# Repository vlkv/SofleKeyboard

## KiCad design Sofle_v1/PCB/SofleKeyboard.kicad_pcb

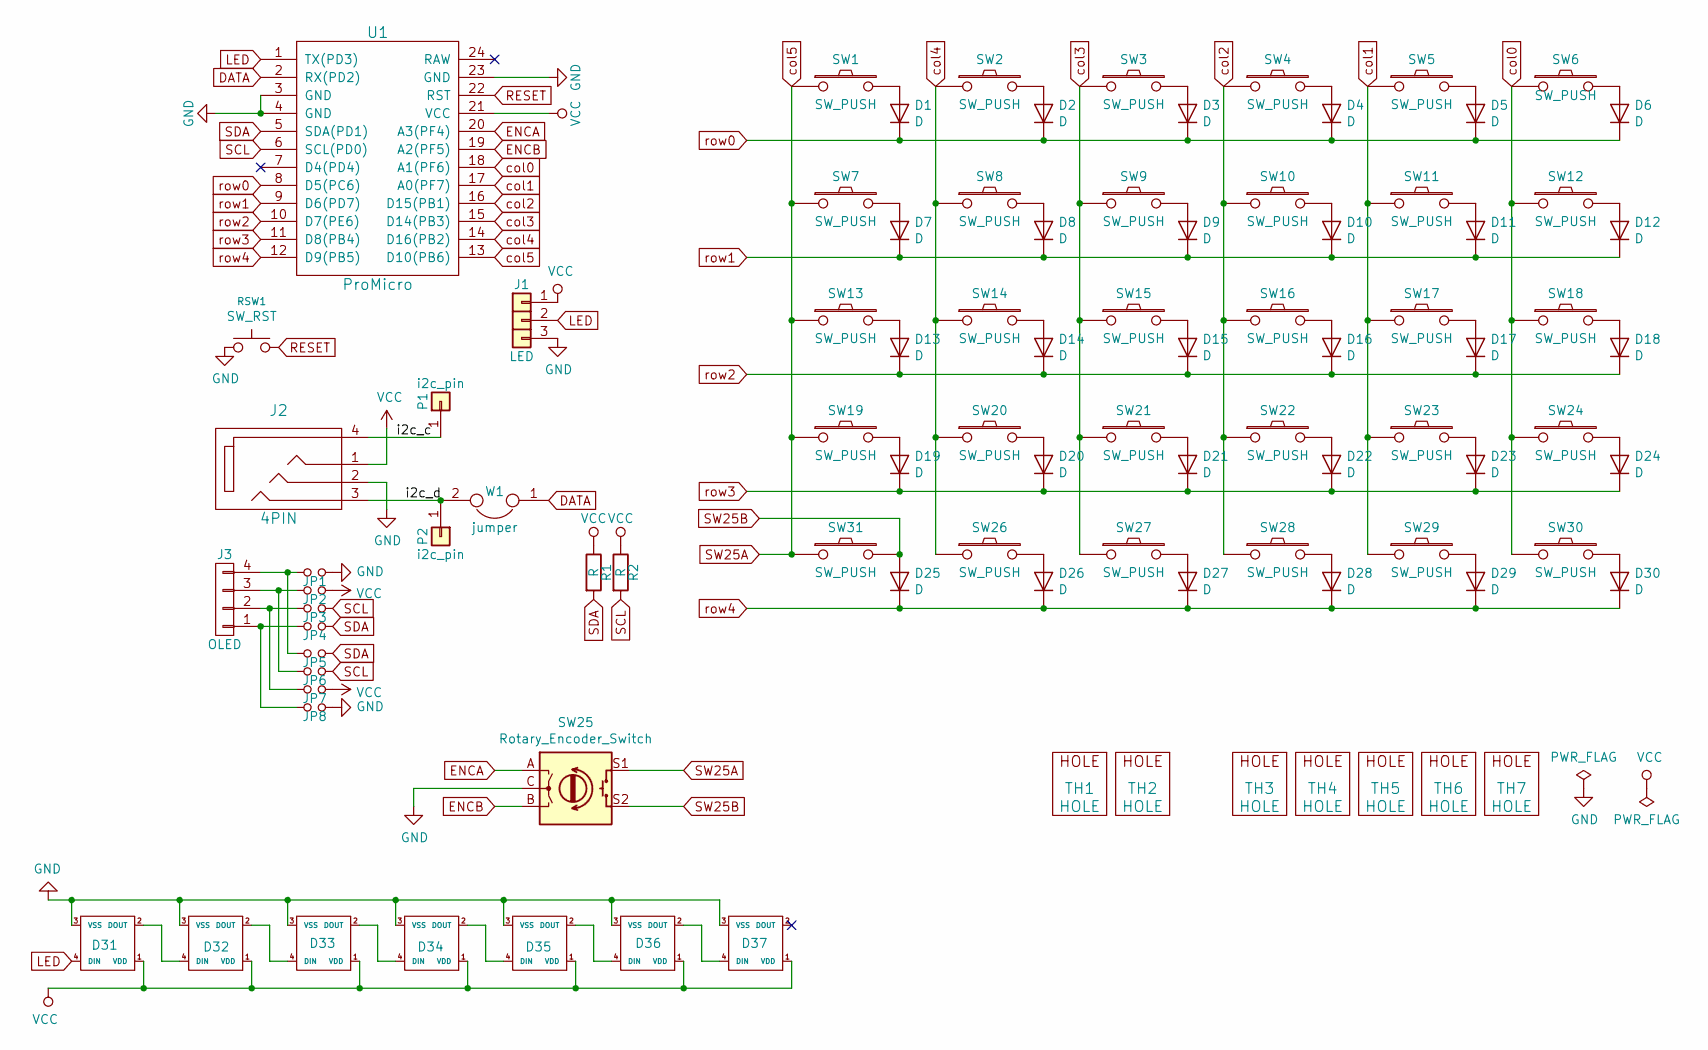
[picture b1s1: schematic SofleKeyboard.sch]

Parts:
D1, D2, D3, D4, D5, D6, D7, D8, D9, D10, D11, D12, D13, D14, D15, D16, D17, D18, D19, D20, D21, D22, D23, D24, D25, D26, D27, D28, D29, D30: D; Diode_SOD123
D31, D32, D33, D34, D35, D36, D37: SK6812MINI; YS-SK6812MINI-E_backlight
J1: LED
J2: 4PIN; MJ-4PP-9
J3: OLED; OLED_4Pin
JP1, JP2, JP3, JP4, JP5, JP6, JP7, JP8: Jumper_NO_Small; Jumper
P1, P2: i2c_pin; 1pin_conn
R1, R2: R; RESISTOR_mini
RSW1: SW_RST; TACT_SWITCH_TVBP06
SW1, SW2, SW3, SW4, SW5, SW6, SW7, SW8, SW9, SW10, SW11, SW12, SW13, SW14, SW15, SW16, SW17, SW18, SW19, SW20, SW21, SW22, SW23, SW24, SW26, SW27, SW28, SW29, SW30, SW31: SW_PUSH; CherryMX_Hotswap
SW25: Rotary_Encoder_Switch; RotaryEncoder_Alps_EC11E-Switch_Vertical_H20mm-keebio_modif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
TH1, TH2: HOLE; M2_HOLE_PCB
TH3, TH4, TH5, TH6, TH7: HOLE; HOLE_M2_TH
U1: ProMicro
W1: jumper; jumper_data

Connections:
/i2c_c: J2.4, P1.1
/i2c_d: J2.3, P2.1, W1.2
DATA: U1.2 (RX(PD2)), W1.1
ENCA: SW25.A, U1.20 (A3(PF4))
ENCB: SW25.B, U1.19 (A2(PF5))
GND: D31.3 (VSS), D32.3 (VSS), D33.3 (VSS), D34.3 (VSS), D35.3 (VSS), D36.3 (VSS), D37.3 (VSS), J1.3, J2.2, JP1.2, JP8.2, RSW1.1, SW25.C, U1.3 (GND), U1.4 (GND), U1.23 (GND)
LED: D31.4 (DIN), J1.2, U1.1 (TX(PD3))
unnamed: D1.2 (A), SW1.2
unnamed: D2.2 (A), SW2.2
unnamed: D3.2 (A), SW3.2
unnamed: D4.2 (A), SW4.2
unnamed: D5.2 (A), SW5.2
unnamed: D6.2 (A), SW6.2
unnamed: D7.2 (A), SW7.2
unnamed: D8.2 (A), SW8.2
unnamed: D9.2 (A), SW9.2
unnamed: D10.2 (A), SW10.2
unnamed: D11.2 (A), SW11.2
unnamed: D12.2 (A), SW12.2
unnamed: D13.2 (A), SW13.2
unnamed: D14.2 (A), SW14.2
unnamed: D15.2 (A), SW15.2
unnamed: D16.2 (A), SW16.2
unnamed: D17.2 (A), SW17.2
unnamed: D18.2 (A), SW18.2
unnamed: D19.2 (A), SW19.2
unnamed: D20.2 (A), SW20.2
unnamed: D21.2 (A), SW21.2
unnamed: D22.2 (A), SW22.2
unnamed: D23.2 (A), SW23.2
unnamed: D24.2 (A), SW24.2
unnamed: D26.2 (A), SW26.2
unnamed: D27.2 (A), SW27.2
unnamed: D28.2 (A), SW28.2
unnamed: D29.2 (A), SW29.2
unnamed: D30.2 (A), SW30.2
unnamed: D31.2 (DOUT), D32.4 (DIN)
unnamed: D32.2 (DOUT), D33.4 (DIN)
unnamed: D33.2 (DOUT), D34.4 (DIN)
unnamed: D34.2 (DOUT), D35.4 (DIN)
unnamed: D35.2 (DOUT), D36.4 (DIN)
unnamed: D36.2 (DOUT), D37.4 (DIN)
unnamed: J3.1, JP4.1, JP8.1
unnamed: J3.2, JP3.1, JP7.1
unnamed: J3.3, JP2.1, JP6.1
unnamed: J3.4, JP1.1, JP5.1
RESET: RSW1.2, U1.22 (RST)
SCL: JP3.2, JP6.2, R2.2, U1.6 (SCL(PD0))
SDA: JP4.2, JP5.2, R1.2, U1.5 (SDA(PD1))
SW25A: SW1.1, SW7.1, SW13.1, SW19.1, SW25.S1, SW31.1, U1.13 (D10(PB6))
SW25B: D25.2 (A), SW25.S2, SW31.2
VCC: D31.1 (VDD), D32.1 (VDD), D33.1 (VDD), D34.1 (VDD), D35.1 (VDD), D36.1 (VDD), D37.1 (VDD), J1.1, J2.1, JP2.2, JP7.2, R1.1, R2.1, U1.21 (VCC)
col0: SW6.1, SW12.1, SW18.1, SW24.1, SW30.1, U1.18 (A1(PF6))
col1: SW5.1, SW11.1, SW17.1, SW23.1, SW29.1, U1.17 (A0(PF7))
col2: SW4.1, SW10.1, SW16.1, SW22.1, SW28.1, U1.16 (D15(PB1))
col3: SW3.1, SW9.1, SW15.1, SW21.1, SW27.1, U1.15 (D14(PB3))
col4: SW2.1, SW8.1, SW14.1, SW20.1, SW26.1, U1.14 (D16(PB2))
row0: D1.1 (K), D2.1 (K), D3.1 (K), D4.1 (K), D5.1 (K), D6.1 (K), U1.8 (D5(PC6))
row1: D7.1 (K), D8.1 (K), D9.1 (K), D10.1 (K), D11.1 (K), D12.1 (K), U1.9 (D6(PD7))
row2: D13.1 (K), D14.1 (K), D15.1 (K), D16.1 (K), D17.1 (K), D18.1 (K), U1.10 (D7(PE6))
row3: D19.1 (K), D20.1 (K), D21.1 (K), D22.1 (K), D23.1 (K), D24.1 (K), U1.11 (D8(PB4))
row4: D25.1 (K), D26.1 (K), D27.1 (K), D28.1 (K), D29.1 (K), D30.1 (K), U1.12 (D9(PB5))

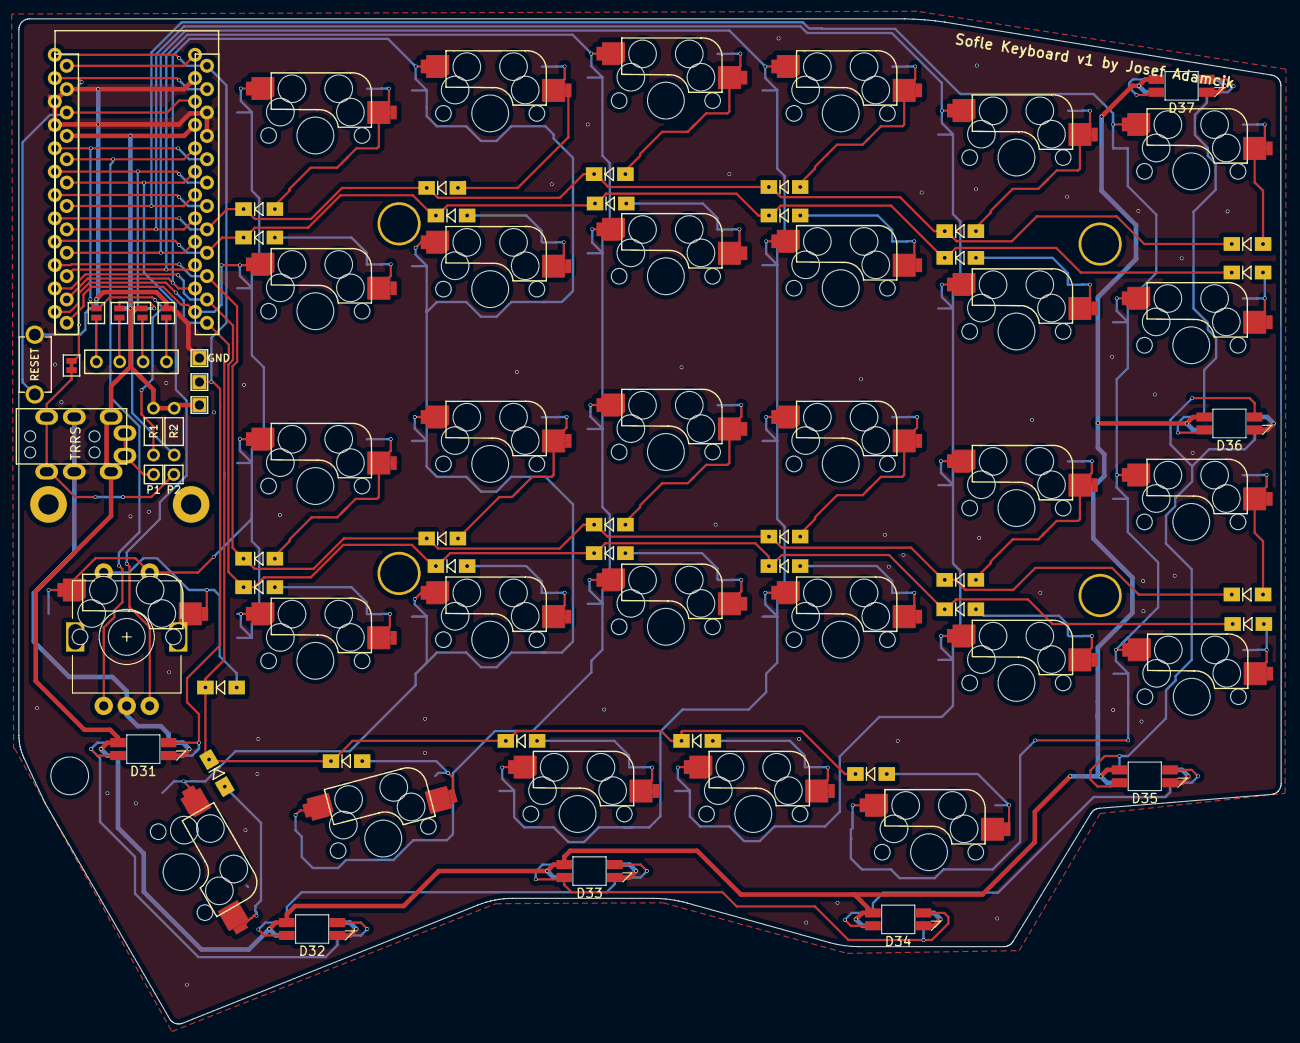
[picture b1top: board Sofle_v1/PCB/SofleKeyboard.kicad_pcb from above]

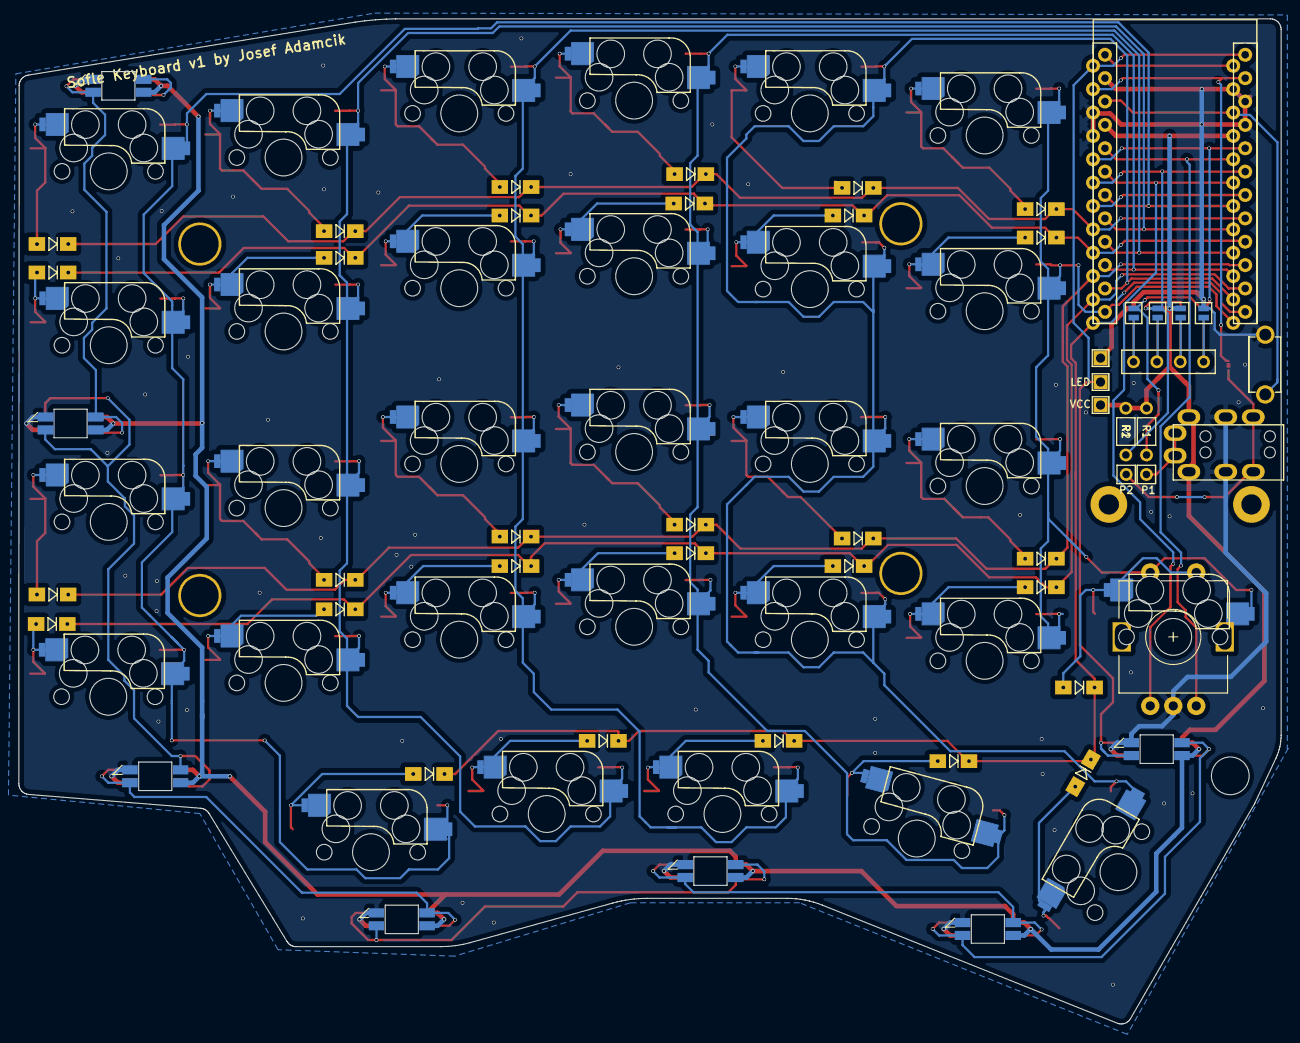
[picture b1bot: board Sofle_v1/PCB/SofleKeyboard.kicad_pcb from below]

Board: 2 copper layers, 137.2 x 109.2 mm, 93 parts (4 on the bottom side), 62 nets.

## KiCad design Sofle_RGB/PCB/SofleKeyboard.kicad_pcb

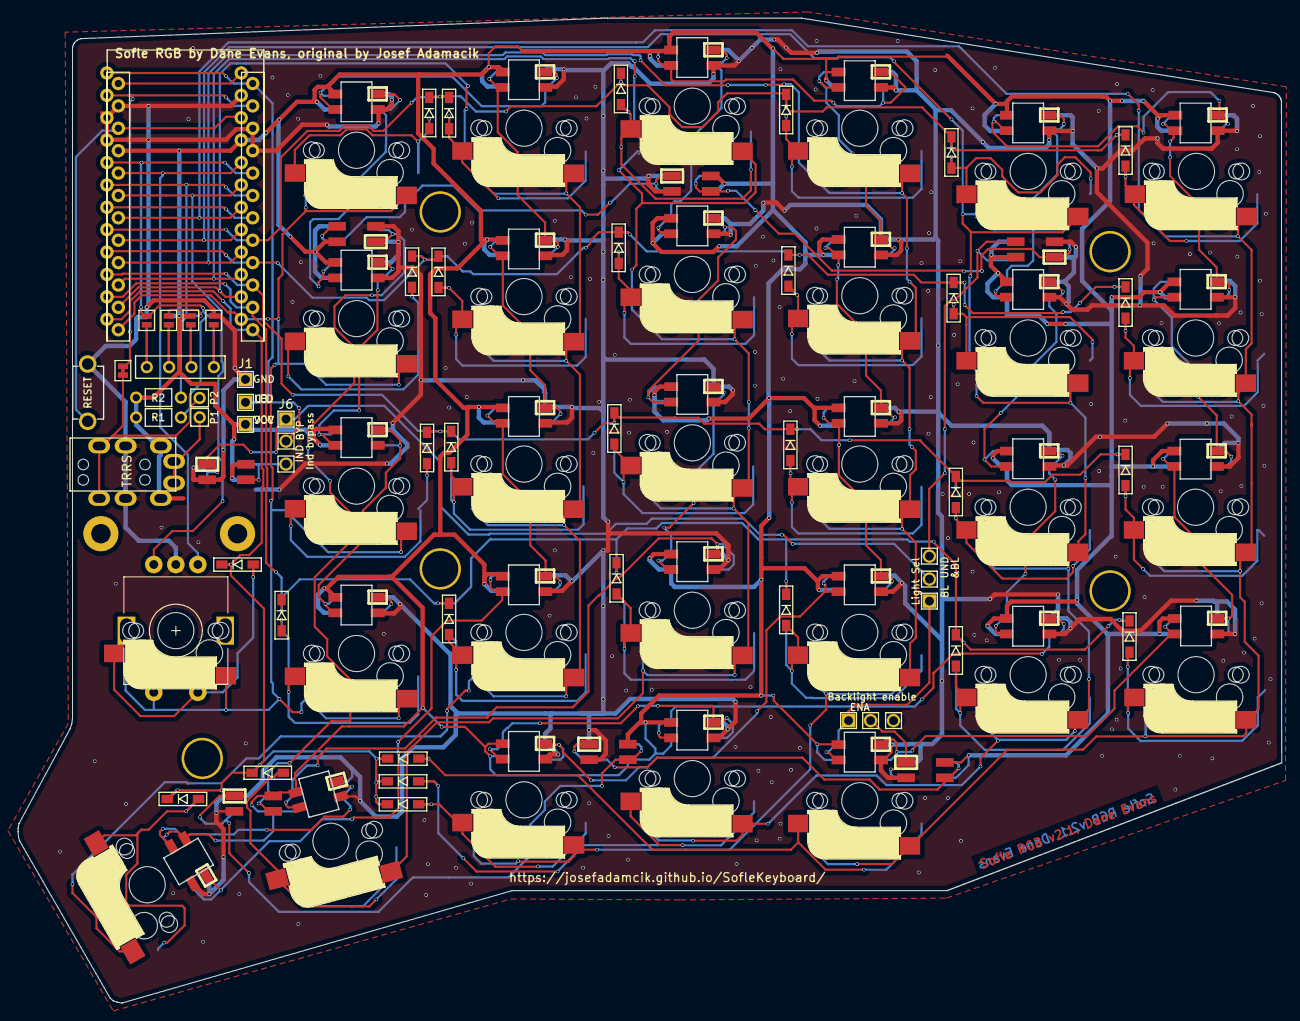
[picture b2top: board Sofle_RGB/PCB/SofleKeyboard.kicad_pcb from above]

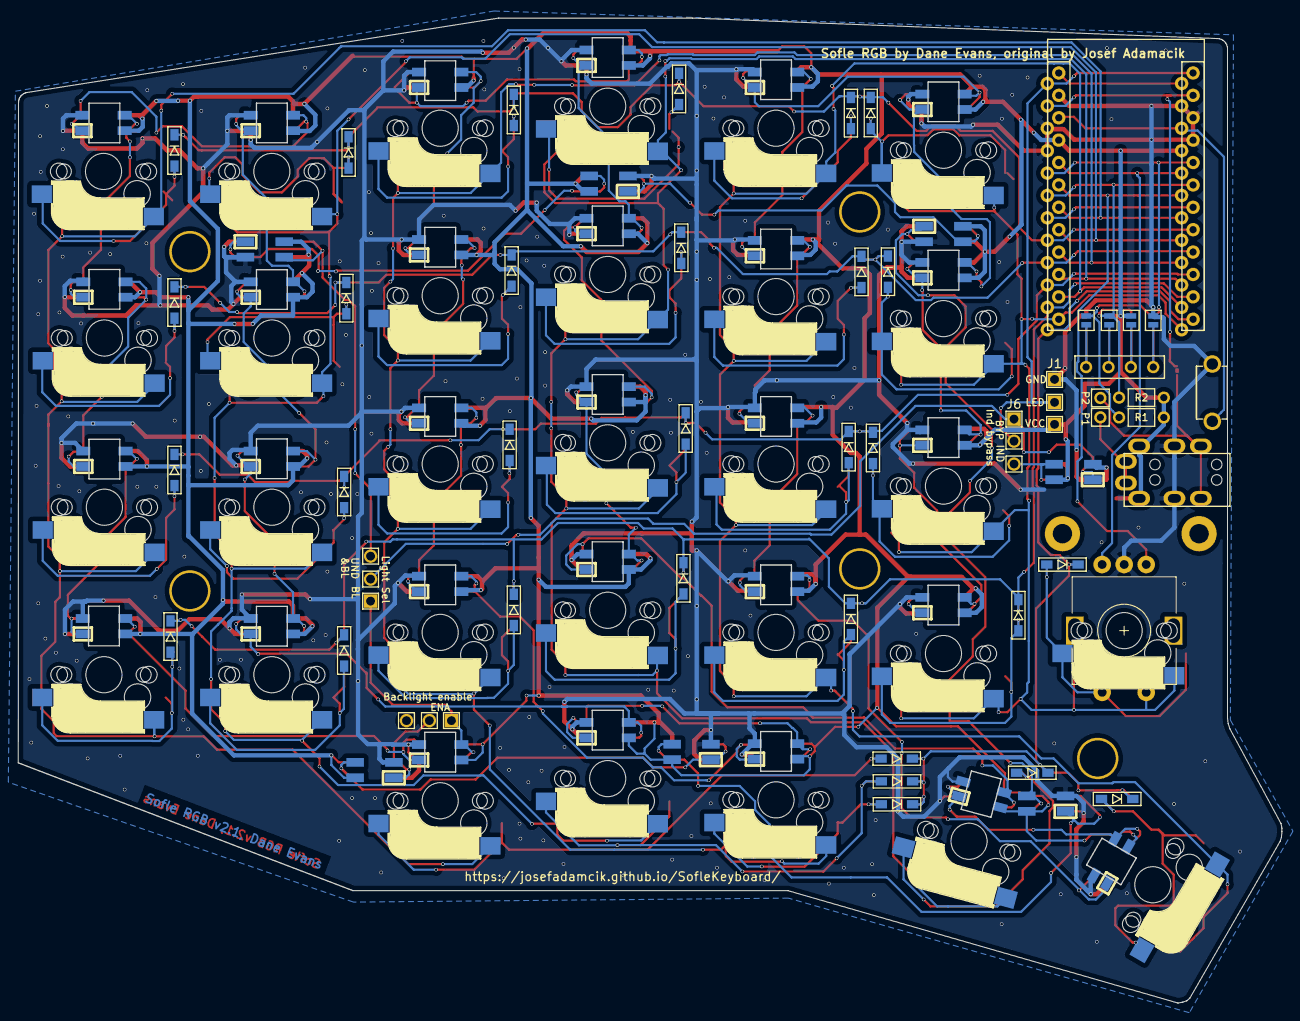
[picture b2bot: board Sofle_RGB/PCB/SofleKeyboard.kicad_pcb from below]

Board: 2 copper layers, 143.4 x 111.8 mm, 96 parts (4 on the bottom side), 94 nets.

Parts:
D1, D2, D3, D4, D5, D6, D7, D8, D9, D10, D11, D12, D13, D14, D15, D16, D17, D18, D19, D20, D21, D22, D23, D24, D25, D26, D27, D28, D29, D30: D; crkbd-diode
D31, D32, D33, D34, D35, D36, D37: LED_sk2812_SM; SK6812MINI_underglow_dev
J1: LED
J2: 4PIN; MJ-4PP-9
J3: OLED; OLED_4Pin
J4: key leds; 3x1header
J5: backlight sel; 3x1header
J6: indicator bypass; 3x1header
JP1, JP2, JP3, JP4, JP5, JP6, JP7, JP8: Jumper_NO_Small; Jumper
P1, P2: i2c_pin; 1pin_conn
R1, R2: R; RESISTOR_mini
RSW1: SW_RST; TACT_SWITCH_TVBP06
SW1, SW2, SW3, SW4, SW5, SW6, SW7, SW8, SW9, SW10, SW11, SW12, SW13, SW14, SW15, SW16, SW17, SW18, SW19, SW20, SW21, SW22, SW23, SW24, SW26, SW27, SW28, SW29, SW30: SW_PUSH-MX_W_LED; SK6812MINI_and_cherry
SW25: Rotary_Encoder_Switch; RotaryEncoder_Alps_EC11E-Switch_Vertical_H20mm-keebio_modif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
SW31: SW_PUSH-MX_W_LED; cherry_mx
TH1, TH2: HOLE; M2_HOLE_PCB
TH3, TH4, TH5, TH6, TH7: HOLE; HOLE_M2_TH
U1: ProMicro
W1: jumper; jumper_data

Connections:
/backlight: J4.1, J5.1, SW30.3
/i2c_c: J2.4, P1.1
/i2c_d: J2.3, P2.1, W1.2
/underglow: D33.3, J4.3
DATA: U1.2, W1.1
ENCA: SW25.A, U1.20
ENCB: SW25.B, U1.19
GND: D31.2, D32.2, D33.2, D34.2, D35.2, D36.2, D37.2, J1.3, J2.2, JP1.2, JP8.2, RSW1.1, SW1.2, SW2.2, SW3.2, SW4.2, SW5.2, SW6.2, SW7.2, SW8.2, SW9.2, SW10.2, SW11.2, SW12.2, SW13.2, SW14.2, SW15.2, SW16.2, SW17.2, SW18.2, SW19.2, SW20.2, SW21.2, SW22.2, SW23.2, SW24.2, SW25.C, SW26.2, SW27.2, SW28.2, SW29.2, SW30.2, U1.3, U1.4, U1.23
LED: J1.2, J6.2, U1.1
unnamed: D1.2, SW1.5
unnamed: D2.2, SW2.5
unnamed: D3.2, SW3.5
unnamed: D4.2, SW4.5
unnamed: D5.2, SW5.5
unnamed: D6.2, SW6.5
unnamed: D7.2, SW7.5
unnamed: D8.2, SW8.5
unnamed: D9.2, SW9.5
unnamed: D10.2, SW10.5
unnamed: D11.2, SW11.5
unnamed: D12.2, SW12.5
unnamed: D13.2, SW13.5
unnamed: D14.2, SW14.5
unnamed: D15.2, SW15.5
unnamed: D16.2, SW16.5
unnamed: D17.2, SW17.5
unnamed: D18.2, SW18.5
unnamed: D19.2, SW19.5
unnamed: D20.2, SW20.5
unnamed: D21.2, SW21.5
unnamed: D22.2, SW22.5
unnamed: D23.2, SW23.5
unnamed: D24.2, SW24.5
unnamed: D26.2, SW26.5
unnamed: D27.2, SW27.5
unnamed: D28.2, SW28.5
unnamed: D29.2, SW29.5
unnamed: D30.2, SW30.5
unnamed: D31.1, D34.3
unnamed: D31.3, D32.1
unnamed: D32.3, D33.1
unnamed: D34.1, D35.3
unnamed: D35.1, D36.3
unnamed: D36.1, J5.2
unnamed: D37.3, J6.3
unnamed: J3.1, JP4.1, JP8.1
unnamed: J3.2, JP3.1, JP7.1
unnamed: J3.3, JP2.1, JP6.1
unnamed: J3.4, JP1.1, JP5.1
unnamed: SW1.1, SW7.3
unnamed: SW1.3, SW2.1
unnamed: SW2.3, SW8.1
unnamed: SW3.1, SW9.3
unnamed: SW3.3, SW4.1
unnamed: SW5.3, SW6.1
unnamed: SW4.3, SW10.1
unnamed: SW10.3, SW16.1
unnamed: SW11.1, SW17.3
unnamed: SW5.1, SW11.3
unnamed: SW6.3, SW12.1
unnamed: SW12.3, SW18.1
unnamed: SW13.1, SW19.3
unnamed: SW7.1, SW13.3
unnamed: SW8.3, SW14.1
unnamed: SW14.3, SW20.1
unnamed: SW15.1, SW21.3
unnamed: SW9.1, SW15.3
unnamed: SW16.3, SW22.1
unnamed: SW17.1, SW23.3
unnamed: SW18.3, SW24.1
unnamed: SW20.3, SW26.1
unnamed: SW21.1, SW27.3
unnamed: SW22.3, SW28.1
unnamed: SW23.1, SW29.3
unnamed: SW24.3, SW30.1
unnamed: SW26.3, SW27.1
unnamed: SW28.3, SW29.1
RESET: RSW1.2, U1.22
SCL: JP3.2, JP6.2, R2.2, U1.6
SDA: JP4.2, JP5.2, R1.2, U1.5
SW25A: SW1.6, SW7.6, SW13.6, SW19.6, SW25.S1, SW31.6, U1.13
SW25B: D25.2, SW25.S2, SW31.5
VCC: D31.4, D32.4, D33.4, D34.4, D35.4, D36.4, D37.4, J1.1, J2.1, JP2.2, JP7.2, R1.1, R2.1, SW1.4, SW2.4, SW3.4, SW4.4, SW5.4, SW6.4, SW7.4, SW8.4, SW9.4, SW10.4, SW11.4, SW12.4, SW13.4, SW14.4, SW15.4, SW16.4, SW17.4, SW18.4, SW19.4, SW20.4, SW21.4, SW22.4, SW23.4, SW24.4, SW26.4, SW27.4, SW28.4, SW29.4, SW30.4, U1.21
col0: SW6.6, SW12.6, SW18.6, SW24.6, SW30.6, U1.18
col1: SW5.6, SW11.6, SW17.6, SW23.6, SW29.6, U1.17
col2: SW4.6, SW10.6, SW16.6, SW22.6, SW28.6, U1.16
col3: SW3.6, SW9.6, SW15.6, SW21.6, SW27.6, U1.15
col4: SW2.6, SW8.6, SW14.6, SW20.6, SW26.6, U1.14
lights: D37.1, J4.2, J6.1
row0: D1.1, D2.1, D3.1, D4.1, D5.1, D6.1, U1.8
row1: D7.1, D8.1, D9.1, D10.1, D11.1, D12.1, U1.9
row2: D13.1, D14.1, D15.1, D16.1, D17.1, D18.1, U1.10
row3: D19.1, D20.1, D21.1, D22.1, D23.1, D24.1, U1.11
row4: D25.1, D26.1, D27.1, D28.1, D29.1, D30.1, U1.12

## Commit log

2022-01-10 Added SW31 into the place where the encoder is located.
2022-01-10 Removed kailh support from the switch footprint
2022-01-10 Fixed routing after footprint change
2022-01-10 Done with the scheme and positioning of the footprints. Started drawing the tracks
2022-01-10 Done with the routing tracks in Sofle v1
2022-01-11 Made one hole without copper
2022-01-26 Fixed the mounting holes
